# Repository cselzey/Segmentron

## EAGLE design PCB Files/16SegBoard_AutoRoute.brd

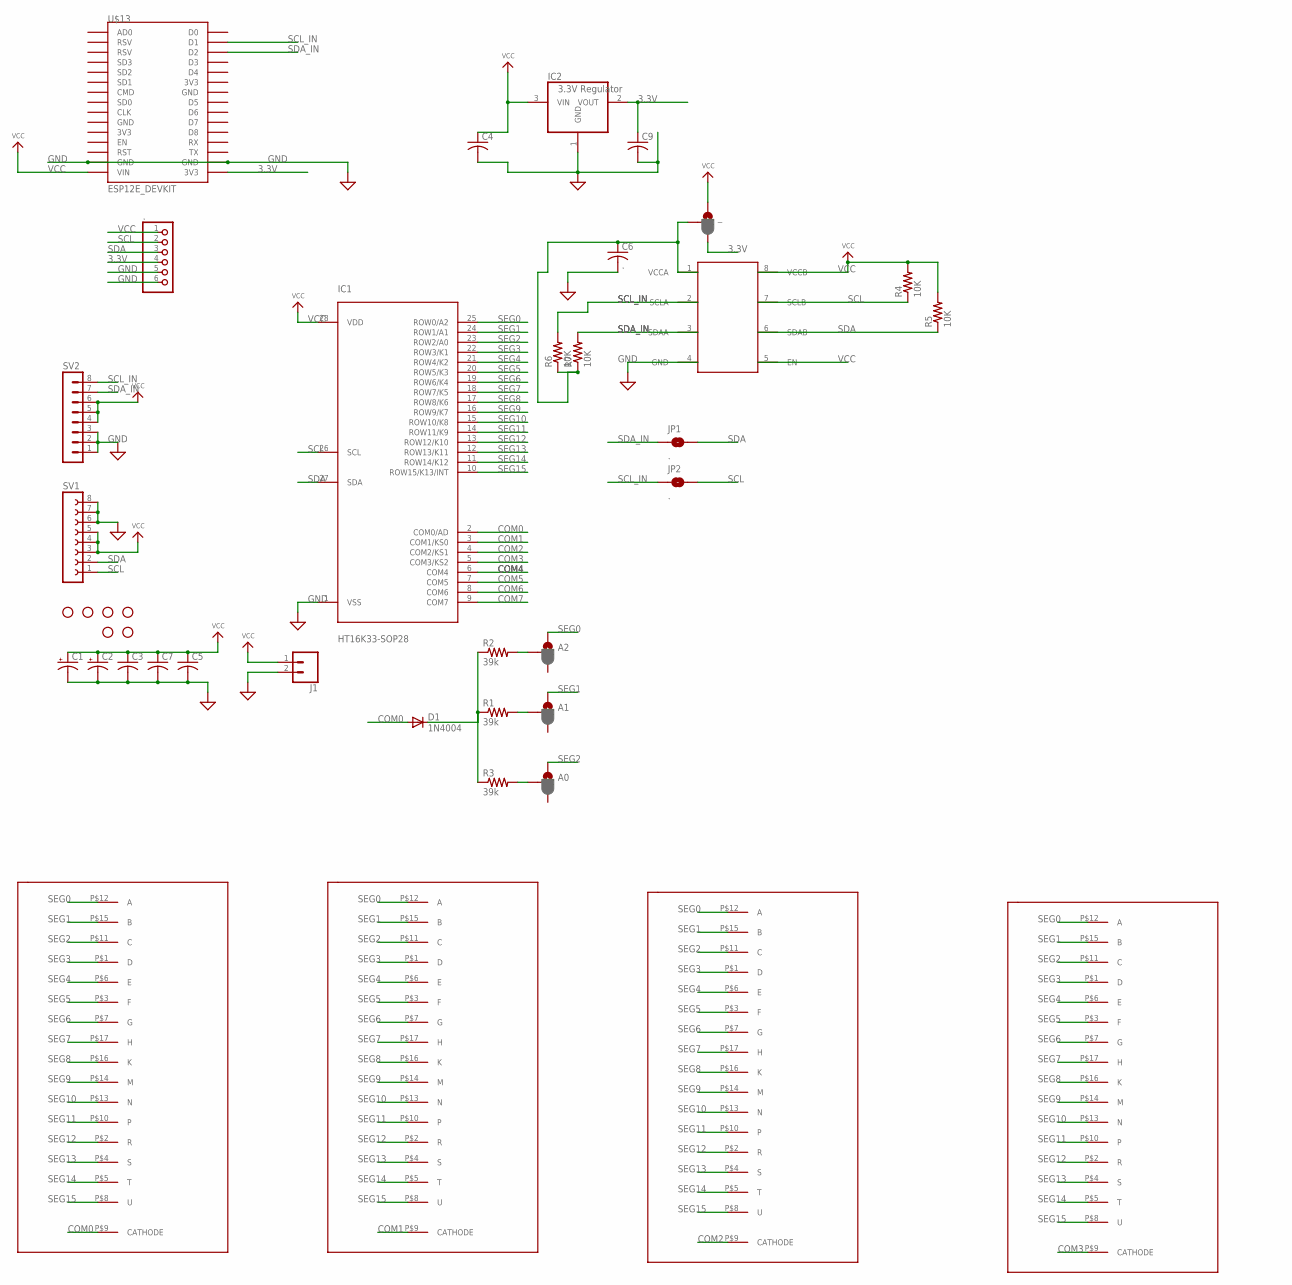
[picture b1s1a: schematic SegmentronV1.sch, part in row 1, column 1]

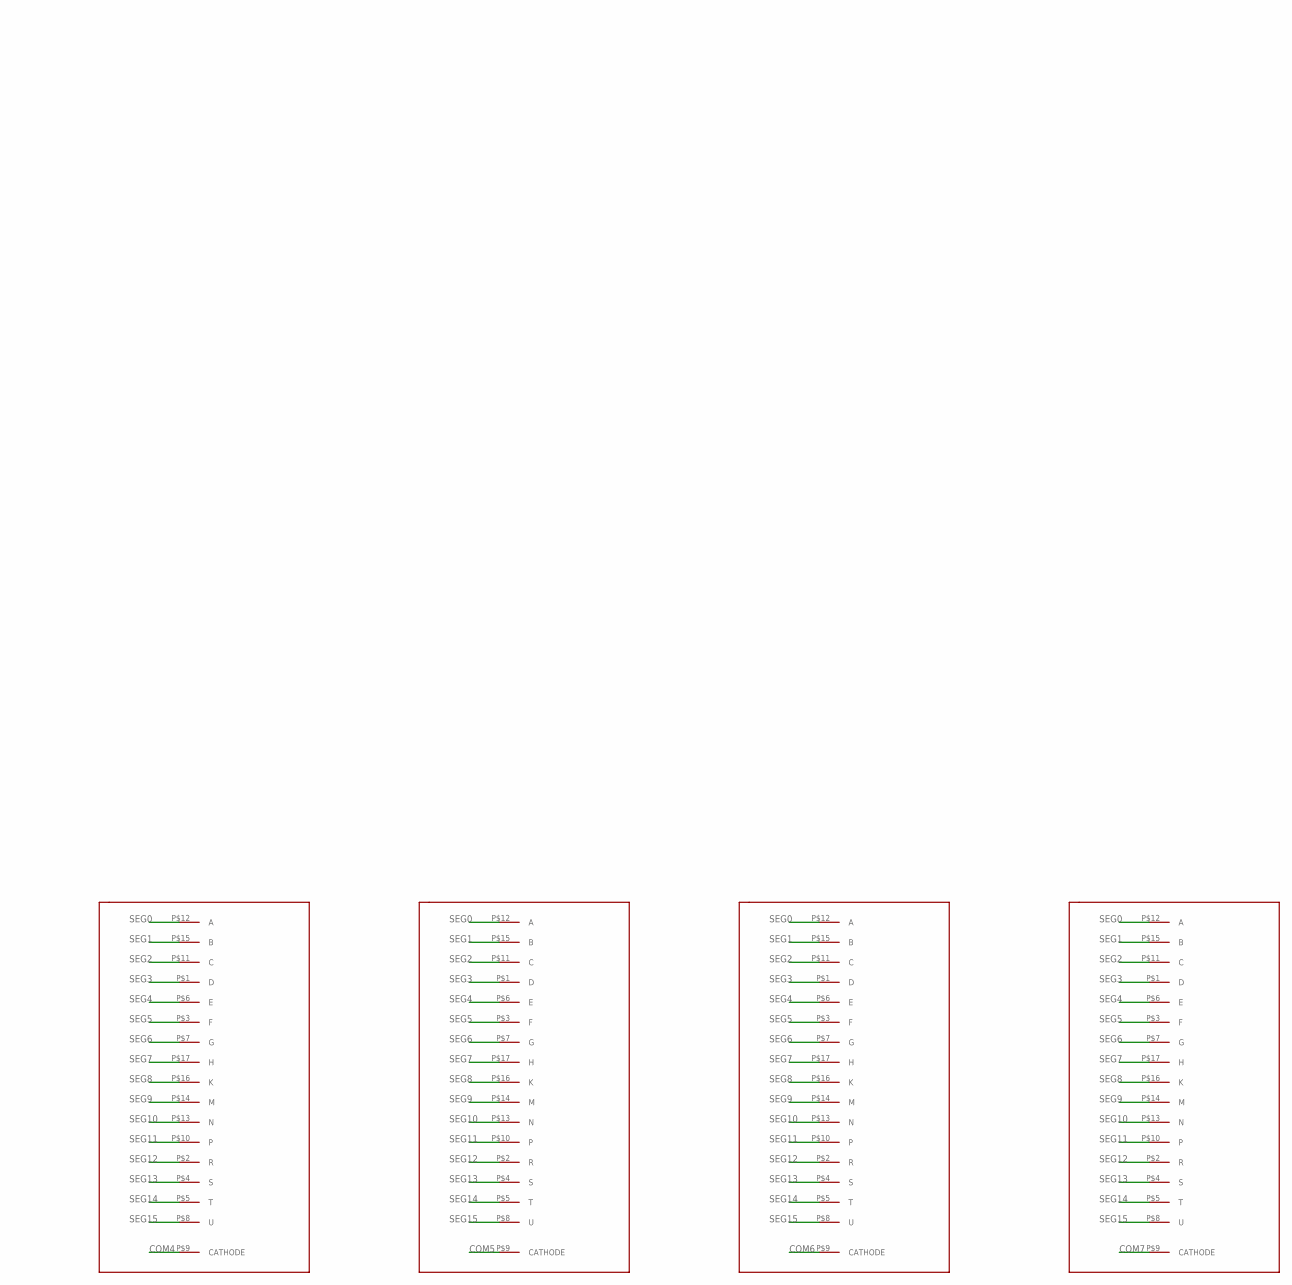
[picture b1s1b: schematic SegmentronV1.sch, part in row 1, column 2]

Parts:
.: PINHD-1X6; 1X06
A0, A1, A2: JUMPER-SMT_3_1-NC_PASTE_SILK; SMT-JUMPER_3_1-NC_PASTE_SILK
C1, C2: CPOL-USE2.5-6; E2,5-6
C3, C4, C7, C9: C-USC0805; C0805
C5: C-US025-030X050; C025-030X050
C6: .; C0805
D1: 1N4004; DO41-10
H1, H2, H3, H4, H5, H6: STAND-OFF
IC1: HT16K33-SOP28; SOIC127P1031X264-28N
IC2: 3.3V Regulator; SOT223
J1: CONN_025MM; SCREWTERMINAL-5MM-2
JP1, JP2: .; SMT-JUMPER_2_NO_NO-SILK
R1, R2, R3: 39k; M1206
R4, R5, R6, R7: 10K; R1206
SV1: FE08W
SV2: MA08-1W
TCA9517: TCA9517; SOIC-8
U$1, U$2, U$3, U$4, U$5, U$6, U$7, U$8: 16SEG; 16SEGLARGE_PKG
U$13: ESP12E_DEVKIT
_: JUMPER-SMT_3_1-NC_PASTE_SILK; SMT-JUMPER_3_1-NC_PASTE_SILK

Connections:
3.3V: ..4, C9.1, IC2.2 (VOUT), U$13.3V3@2 (3V3), _.3
COM0: D1.A, IC1.2 (COM0/AD), U$1.P$9 (CATHODE)
COM1: IC1.3 (COM1/KS0), U$2.P$9 (CATHODE)
COM2: IC1.4 (COM2/KS1), U$3.P$9 (CATHODE)
COM3: IC1.5 (COM3/KS2), U$4.P$9 (CATHODE)
COM4: IC1.6 (COM4), U$5.P$9 (CATHODE)
COM5: IC1.7 (COM5), U$6.P$9 (CATHODE)
COM6: IC1.8 (COM6), U$7.P$9 (CATHODE)
COM7: IC1.9 (COM7), U$8.P$9 (CATHODE)
GND: ..5, ..6, C1.-, C2.-, C3.2, C4.2, C5.2, C6.2, C7.2, C9.2, IC1.1 (VSS), IC2.1 (GND), J1.2, SV1.6, SV1.7, SV1.8, SV2.1, SV2.2, SV2.3, TCA9517.4 (GND), U$13.GND@1 (GND), U$13.GND@3 (GND)
unnamed: D1.C, R1.1, R2.1, R3.1
unnamed: A0.2, R3.2
unnamed: A1.2, R1.2
unnamed: A2.2, R2.2
unnamed: C6.1, R6.1, R7.1, TCA9517.1 (VCCA), _.2
SCL: ..2, IC1.26 (SCL), JP2.2, R4.1, SV1.1, TCA9517.7 (SCLB)
SCL_IN: JP2.1, R6.2, SV2.8, TCA9517.2 (SCLA), U$13.D1
SDA: ..3, IC1.27 (SDA), JP1.2, R5.1, SV1.2, TCA9517.6 (SDAB)
SDA_IN: JP1.1, R7.2, SV2.7, TCA9517.3 (SDAA), U$13.D2
SEG0: A2.1, IC1.25 (ROW0/A2), U$1.P$12 (A), U$2.P$12 (A), U$3.P$12 (A), U$4.P$12 (A), U$5.P$12 (A), U$6.P$12 (A), U$7.P$12 (A), U$8.P$12 (A)
SEG1: A1.1, IC1.24 (ROW1/A1), U$1.P$15 (B), U$2.P$15 (B), U$3.P$15 (B), U$4.P$15 (B), U$5.P$15 (B), U$6.P$15 (B), U$7.P$15 (B), U$8.P$15 (B)
SEG2: A0.1, IC1.23 (ROW2/A0), U$1.P$11 (C), U$2.P$11 (C), U$3.P$11 (C), U$4.P$11 (C), U$5.P$11 (C), U$6.P$11 (C), U$7.P$11 (C), U$8.P$11 (C)
SEG3: IC1.22 (ROW3/K1), U$1.P$1 (D), U$2.P$1 (D), U$3.P$1 (D), U$4.P$1 (D), U$5.P$1 (D), U$6.P$1 (D), U$7.P$1 (D), U$8.P$1 (D)
SEG4: IC1.21 (ROW4/K2), U$1.P$6 (E), U$2.P$6 (E), U$3.P$6 (E), U$4.P$6 (E), U$5.P$6 (E), U$6.P$6 (E), U$7.P$6 (E), U$8.P$6 (E)
SEG5: IC1.20 (ROW5/K3), U$1.P$3 (F), U$2.P$3 (F), U$3.P$3 (F), U$4.P$3 (F), U$5.P$3 (F), U$6.P$3 (F), U$7.P$3 (F), U$8.P$3 (F)
SEG6: IC1.19 (ROW6/K4), U$1.P$7 (G), U$2.P$7 (G), U$3.P$7 (G), U$4.P$7 (G), U$5.P$7 (G), U$6.P$7 (G), U$7.P$7 (G), U$8.P$7 (G)
SEG7: IC1.18 (ROW7/K5), U$1.P$17 (H), U$2.P$17 (H), U$3.P$17 (H), U$4.P$17 (H), U$5.P$17 (H), U$6.P$17 (H), U$7.P$17 (H), U$8.P$17 (H)
SEG8: IC1.17 (ROW8/K6), U$1.P$16 (K), U$2.P$16 (K), U$3.P$16 (K), U$4.P$16 (K), U$5.P$16 (K), U$6.P$16 (K), U$7.P$16 (K), U$8.P$16 (K)
SEG9: IC1.16 (ROW9/K7), U$1.P$14 (M), U$2.P$14 (M), U$3.P$14 (M), U$4.P$14 (M), U$5.P$14 (M), U$6.P$14 (M), U$7.P$14 (M), U$8.P$14 (M)
SEG10: IC1.15 (ROW10/K8), U$1.P$13 (N), U$2.P$13 (N), U$3.P$13 (N), U$4.P$13 (N), U$5.P$13 (N), U$6.P$13 (N), U$7.P$13 (N), U$8.P$13 (N)
SEG11: IC1.14 (ROW11/K9), U$1.P$10, U$2.P$10, U$3.P$10, U$4.P$10, U$5.P$10, U$6.P$10, U$7.P$10, U$8.P$10
SEG12: IC1.13 (ROW12/K10), U$1.P$2 (R), U$2.P$2 (R), U$3.P$2 (R), U$4.P$2 (R), U$5.P$2 (R), U$6.P$2 (R), U$7.P$2 (R), U$8.P$2 (R)
SEG13: IC1.12 (ROW13/K11), U$1.P$4 (S), U$2.P$4 (S), U$3.P$4 (S), U$4.P$4 (S), U$5.P$4 (S), U$6.P$4 (S), U$7.P$4 (S), U$8.P$4 (S)
SEG14: IC1.11 (ROW14/K12), U$1.P$5 (T), U$2.P$5 (T), U$3.P$5 (T), U$4.P$5 (T), U$5.P$5 (T), U$6.P$5 (T), U$7.P$5 (T), U$8.P$5 (T)
SEG15: IC1.10 (ROW15/K13/INT), U$1.P$8 (U), U$2.P$8 (U), U$3.P$8 (U), U$4.P$8 (U), U$5.P$8 (U), U$6.P$8 (U), U$7.P$8 (U), U$8.P$8 (U)
VCC: ..1, C1.+, C2.+, C3.1, C4.1, C5.1, C7.1, IC1.28 (VDD), IC2.3 (VIN), J1.1, R4.2, R5.2, SV1.3, SV1.4, SV1.5, SV2.4, SV2.5, SV2.6, TCA9517.5 (EN), TCA9517.8 (VCCB), U$13.VIN, _.1

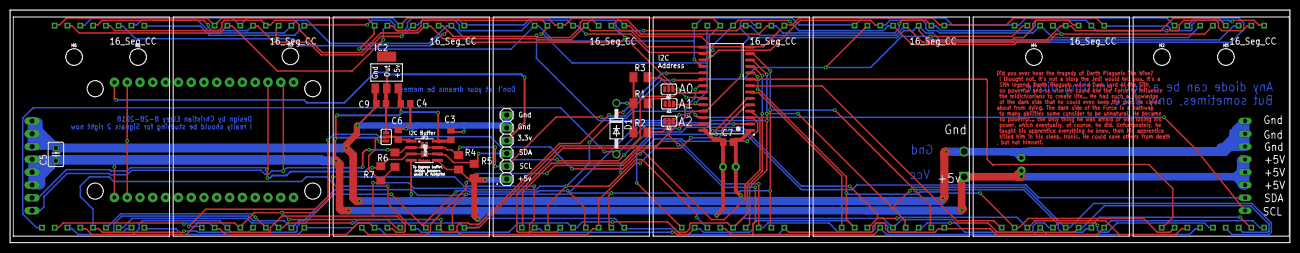
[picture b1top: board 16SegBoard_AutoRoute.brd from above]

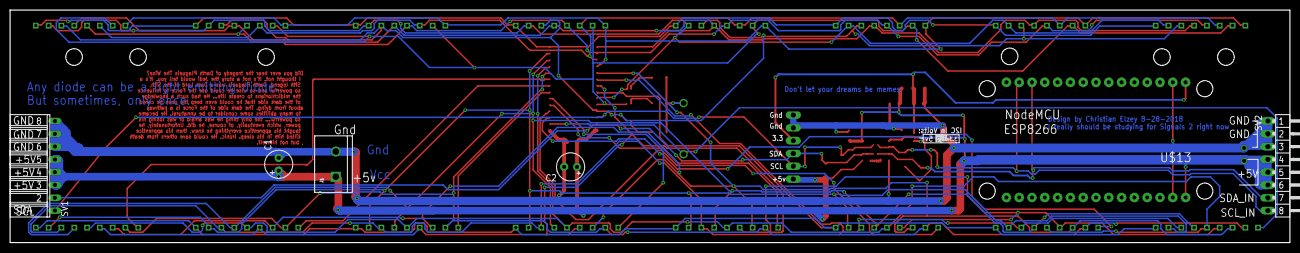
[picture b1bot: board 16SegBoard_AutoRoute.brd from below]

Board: 2 copper layers, 254.0 x 46.1 mm, 44 parts (6 on the bottom side), 36 nets.

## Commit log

2018-09-10 Initial Commit
    See above
2018-09-11 Got rid of Segmentron.h and Segmentron.cpp, which now live in the Segmentron_Lib folder
2018-09-11 Renamed PCB files

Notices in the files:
parts and their libraries:
SparkFun-Connectors: Licensing: Creative Commons ShareAlike 4.0 International - https://creativecommons.org/licenses/by-sa/4.0
